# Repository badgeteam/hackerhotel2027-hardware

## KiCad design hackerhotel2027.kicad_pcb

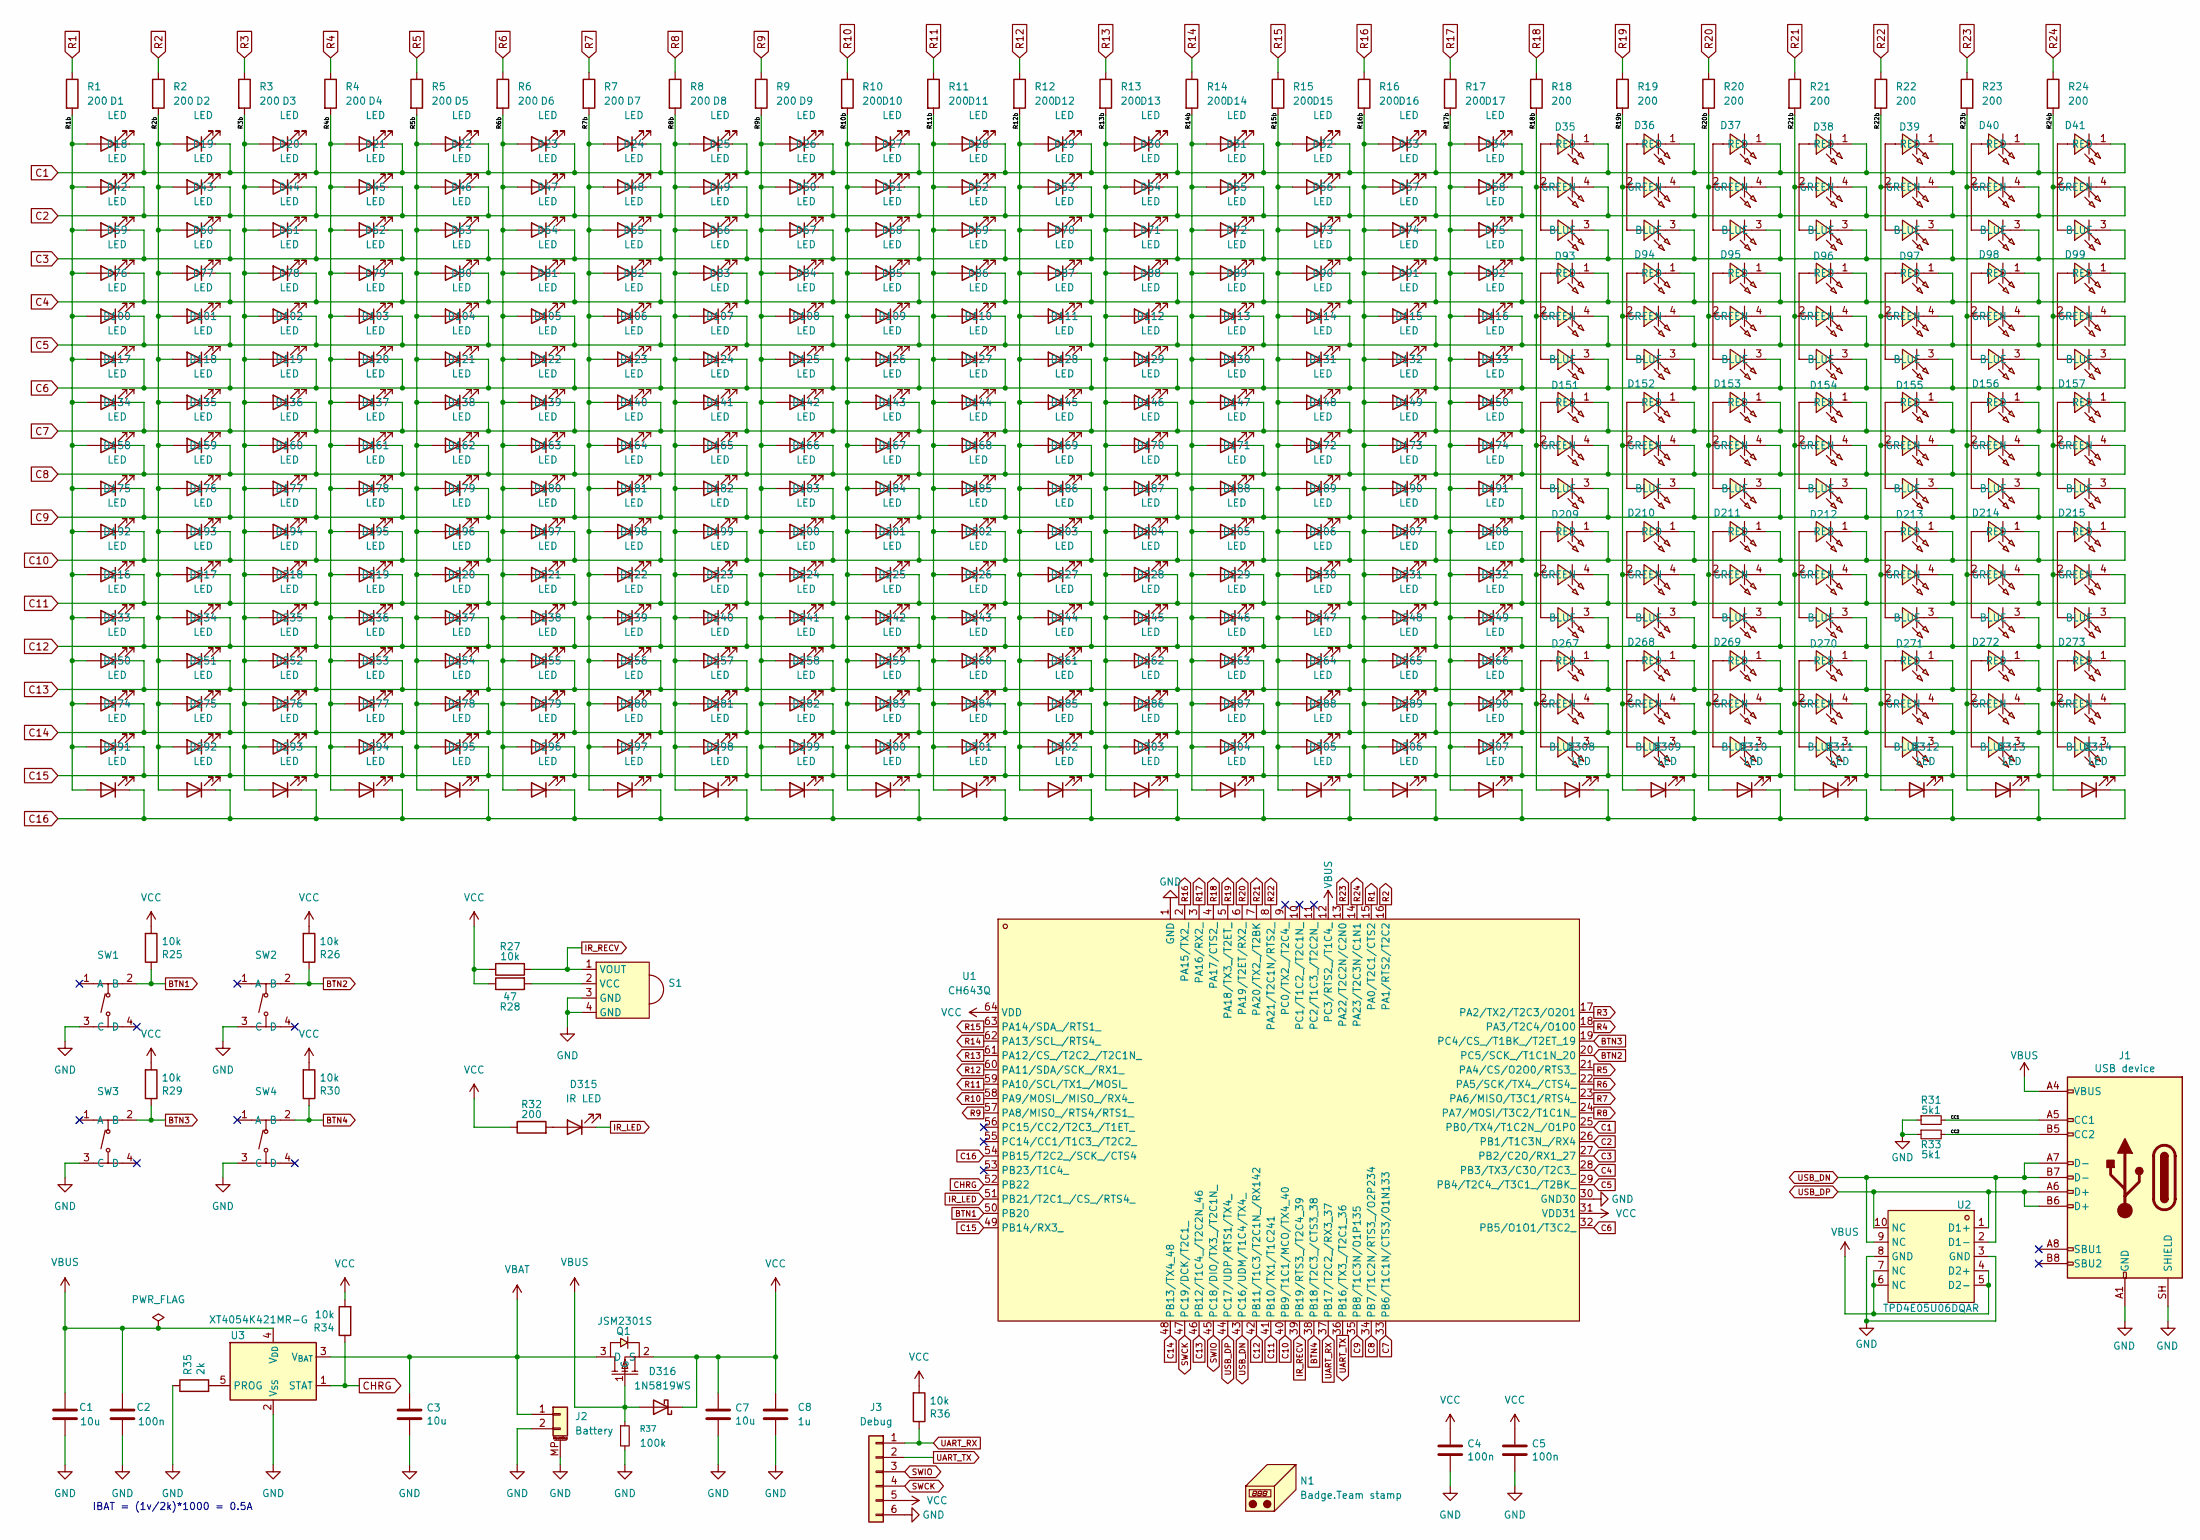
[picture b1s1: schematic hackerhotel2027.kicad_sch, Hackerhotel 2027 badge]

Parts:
C1, C3, C7: 10u; C_0603_1608Metric; LCSC Part C19702
C2: 100n; C_0402_1005Metric; LCSC Part C1525
C4, C5: 100n; C_0402_1005Metric; LCSC Part C307331
C8: 1u; C_0603_1608Metric; LCSC Part C5199872
D1, D2, D3, D4, D5, D6, D7, D8, D9, D10, D11, D12, D13, D14, D15, D16, D17, D18, D19, D20, D21, D22, D23, D24, D25, D26, D27, D28, D29, D30, D31, D32, D33, D34, D42, D43, D44, D45, D46, D47, D48, D49, D50, D51, D52, D53, D54, D55, D56, D57, D58, D59, D60, D61, D62, D63, D64, D65, D66, D67, D68, D69, D70, D71, D72, D73, D74, D75, D76, D77, D78, D79, D80, D81, D82, D83, D84, D85, D86, D87, D88, D89, D90, D91, D92, D100, D101, D102, D103, D104, D105, D106, D107, D108, D109, D110, D111, D112, D113, D114, D115, D116, D117, D118, D119, D120, D121, D122, D123, D124, D125, D126, D127, D128, D129, D130, D131, D132, D133, D134, D135, D136, D137, D138, D139, D140, D141, D142, D143, D144, D145, D146, D147, D148, D149, D150, D158, D159, D160, D161, D162, D163, D164, D165, D166, D167, D168, D169, D170, D171, D172, D173, D174, D175, D176, D177, D178, D179, D180, D181, D182, D183, D184, D185, D186, D187, D188, D189, D190, D191, D192, D193, D194, D195, D196, D197, D198, D199, D200, D201, D202, D203, D204, D205, D206, D207, D208, D216, D217, D218, D219, D220, D221, D222, D223, D224, D225, D226, D227, D228, D229, D230, D231, D232, D233, D234, D235, D236, D237, D238, D239, D240, D241, D242, D243, D244, D245, D246, D247, D248, D249, D250, D251, D252, D253, D254, D255, D256, D257, D258, D259, D260, D261, D262, D263, D264, D265, D266, D274, D275, D276, D277, D278, D279, D280, D281, D282, D283, D284, D285, D286, D287, D288, D289, D290, D291, D292, D293, D294, D295, D296, D297, D298, D299, D300, D301, D302, D303, D304, D305, D306, D307, D308, D309, D310, D311, D312, D313, D314: LED; LED_0402_1005Metric_nosilk; LCSC Part C52675968
D35, D36, D37, D38, D39, D40, D41, D93, D94, D95, D96, D97, D98, D99, D151, D152, D153, D154, D155, D156, D157, D209, D210, D211, D212, D213, D214, D215, D267, D268, D269, D270, D271, D272, D273: NH-B1515RGBA-GF; LED-SMD-4P-L1.6-W1.5_NH-B1515RGBA-GF; MPN NH-B1515RGBA-GF; LCSC Part C52212029
D315: IR LED; LED_0603_1608Metric; LCSC Part C965886
D316: 1N5819WS; D_SOD-323; LCSC Part C191023
J1: USB device; USB_C_Receptacle_HRO_TYPE-C-31-M-12; LCSC Part C165948
J2: Battery; CONN-SMD_PH-2AWB; LCSC Part C20598817
J3: Debug; PinHeader_1x06_P1.27mm_Vertical
N1: Badge.Team stamp; stamp_small
Q1: JSM2301S; SOT-23; LCSC Part C916399
R1, R2, R3, R4, R5, R6, R7, R8, R9, R10, R11, R12, R13, R14, R15, R16, R17, R18, R19, R20, R21, R22, R23, R24, R32: 200; R_0402_1005Metric; LCSC Part C25087
R25, R26, R27, R29, R30, R34, R36: 10k; R_0402_1005Metric; LCSC Part C25744
R28: 47; R_0402_1005Metric; LCSC Part C22369545
R31, R33: 5k1; R_0402_1005Metric; LCSC Part C25905
R35: 2k; R_0402_1005Metric; LCSC Part C4109
R37: 100k; R_0402_1005Metric; LCSC Part C25741
S1: DY-IRMHF384-T05-2.5KB; OPTO-SMD_4P-L3.9-W3.4_IRM-H432M3-R8; MPN DY-IRMHF384-T05-2.5KB; LCSC Part C7280961
SW1, SW2, SW3, SW4: TS-1187A-B-A-B; SW-SMD_4P-L5.1-W5.1-P3.70-LS6.5-TL_H1.5; MPN TS-1187A-B-A-B; LCSC Part C318884
U1: CH643Q; LQFP-64_L7.0-W7.0-P0.40-LS9.2-BL; MPN CH643Q; LCSC Part C22448687
U2: TPD4E05U06DQAR; USON-10_L2.5-W1.0-P0.50-BL; LCSC Part C138714
U3: XT4054K421MR-G; SOT-23-5; LCSC Part C141405

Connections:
/CC1: J1.A5 (CC1), R31.2
/CC2: J1.B5 (CC2), R33.2
/R1b: D1.2 (A), D18.2 (A), D42.2 (A), D59.2 (A), D76.2 (A), D100.2 (A), D117.2 (A), D134.2 (A), D158.2 (A), D175.2 (A), D192.2 (A), D216.2 (A), D233.2 (A), D250.2 (A), D274.2 (A), D291.2 (A), R1.2
/R2b: D2.2 (A), D19.2 (A), D43.2 (A), D60.2 (A), D77.2 (A), D101.2 (A), D118.2 (A), D135.2 (A), D159.2 (A), D176.2 (A), D193.2 (A), D217.2 (A), D234.2 (A), D251.2 (A), D275.2 (A), D292.2 (A), R2.2
/R3b: D3.2 (A), D20.2 (A), D44.2 (A), D61.2 (A), D78.2 (A), D102.2 (A), D119.2 (A), D136.2 (A), D160.2 (A), D177.2 (A), D194.2 (A), D218.2 (A), D235.2 (A), D252.2 (A), D276.2 (A), D293.2 (A), R3.2
/R4b: D4.2 (A), D21.2 (A), D45.2 (A), D62.2 (A), D79.2 (A), D103.2 (A), D120.2 (A), D137.2 (A), D161.2 (A), D178.2 (A), D195.2 (A), D219.2 (A), D236.2 (A), D253.2 (A), D277.2 (A), D294.2 (A), R4.2
/R5b: D5.2 (A), D22.2 (A), D46.2 (A), D63.2 (A), D80.2 (A), D104.2 (A), D121.2 (A), D138.2 (A), D162.2 (A), D179.2 (A), D196.2 (A), D220.2 (A), D237.2 (A), D254.2 (A), D278.2 (A), D295.2 (A), R5.2
/R6b: D6.2 (A), D23.2 (A), D47.2 (A), D64.2 (A), D81.2 (A), D105.2 (A), D122.2 (A), D139.2 (A), D163.2 (A), D180.2 (A), D197.2 (A), D221.2 (A), D238.2 (A), D255.2 (A), D279.2 (A), D296.2 (A), R6.2
/R7b: D7.2 (A), D24.2 (A), D48.2 (A), D65.2 (A), D82.2 (A), D106.2 (A), D123.2 (A), D140.2 (A), D164.2 (A), D181.2 (A), D198.2 (A), D222.2 (A), D239.2 (A), D256.2 (A), D280.2 (A), D297.2 (A), R7.2
/R8b: D8.2 (A), D25.2 (A), D49.2 (A), D66.2 (A), D83.2 (A), D107.2 (A), D124.2 (A), D141.2 (A), D165.2 (A), D182.2 (A), D199.2 (A), D223.2 (A), D240.2 (A), D257.2 (A), D281.2 (A), D298.2 (A), R8.2
/R9b: D9.2 (A), D26.2 (A), D50.2 (A), D67.2 (A), D84.2 (A), D108.2 (A), D125.2 (A), D142.2 (A), D166.2 (A), D183.2 (A), D200.2 (A), D224.2 (A), D241.2 (A), D258.2 (A), D282.2 (A), D299.2 (A), R9.2
/R10b: D10.2 (A), D27.2 (A), D51.2 (A), D68.2 (A), D85.2 (A), D109.2 (A), D126.2 (A), D143.2 (A), D167.2 (A), D184.2 (A), D201.2 (A), D225.2 (A), D242.2 (A), D259.2 (A), D283.2 (A), D300.2 (A), R10.2
/R11b: D11.2 (A), D28.2 (A), D52.2 (A), D69.2 (A), D86.2 (A), D110.2 (A), D127.2 (A), D144.2 (A), D168.2 (A), D185.2 (A), D202.2 (A), D226.2 (A), D243.2 (A), D260.2 (A), D284.2 (A), D301.2 (A), R11.2
/R12b: D12.2 (A), D29.2 (A), D53.2 (A), D70.2 (A), D87.2 (A), D111.2 (A), D128.2 (A), D145.2 (A), D169.2 (A), D186.2 (A), D203.2 (A), D227.2 (A), D244.2 (A), D261.2 (A), D285.2 (A), D302.2 (A), R12.2
/R13b: D13.2 (A), D30.2 (A), D54.2 (A), D71.2 (A), D88.2 (A), D112.2 (A), D129.2 (A), D146.2 (A), D170.2 (A), D187.2 (A), D204.2 (A), D228.2 (A), D245.2 (A), D262.2 (A), D286.2 (A), D303.2 (A), R13.2
/R14b: D14.2 (A), D31.2 (A), D55.2 (A), D72.2 (A), D89.2 (A), D113.2 (A), D130.2 (A), D147.2 (A), D171.2 (A), D188.2 (A), D205.2 (A), D229.2 (A), D246.2 (A), D263.2 (A), D287.2 (A), D304.2 (A), R14.2
/R15b: D15.2 (A), D32.2 (A), D56.2 (A), D73.2 (A), D90.2 (A), D114.2 (A), D131.2 (A), D148.2 (A), D172.2 (A), D189.2 (A), D206.2 (A), D230.2 (A), D247.2 (A), D264.2 (A), D288.2 (A), D305.2 (A), R15.2
/R16b: D16.2 (A), D33.2 (A), D57.2 (A), D74.2 (A), D91.2 (A), D115.2 (A), D132.2 (A), D149.2 (A), D173.2 (A), D190.2 (A), D207.2 (A), D231.2 (A), D248.2 (A), D265.2 (A), D289.2 (A), D306.2 (A), R16.2
/R17b: D17.2 (A), D34.2 (A), D58.2 (A), D75.2 (A), D92.2 (A), D116.2 (A), D133.2 (A), D150.2 (A), D174.2 (A), D191.2 (A), D208.2 (A), D232.2 (A), D249.2 (A), D266.2 (A), D290.2 (A), D307.2 (A), R17.2
/R18b: D35.2, D93.2, D151.2, D209.2, D267.2, D308.2 (A), R18.2
/R19b: D36.2, D94.2, D152.2, D210.2, D268.2, D309.2 (A), R19.2
/R20b: D37.2, D95.2, D153.2, D211.2, D269.2, D310.2 (A), R20.2
/R21b: D38.2, D96.2, D154.2, D212.2, D270.2, D311.2 (A), R21.2
/R22b: D39.2, D97.2, D155.2, D213.2, D271.2, D312.2 (A), R22.2
/R23b: D40.2, D98.2, D156.2, D214.2, D272.2, D313.2 (A), R23.2
/R24b: D41.2, D99.2, D157.2, D215.2, D273.2, D314.2 (A), R24.2
BTN1: R25.1, SW1.2 (B), U1.50 (PB20)
BTN2: R26.1, SW2.2 (B), U1.20 (PC5/SCK_/T1C1N_20)
BTN3: R29.1, SW3.2 (B), U1.19 (PC4/CS_/T1BK_/T2ET_19)
BTN4: R30.1, SW4.2 (B), U1.38 (PB18/T2C3_/CTS3_38)
C1: D1.1 (K), D2.1 (K), D3.1 (K), D4.1 (K), D5.1 (K), D6.1 (K), D7.1 (K), D8.1 (K), D9.1 (K), D10.1 (K), D11.1 (K), D12.1 (K), D13.1 (K), D14.1 (K), D15.1 (K), D16.1 (K), D17.1 (K), D35.1 (RED), D36.1 (RED), D37.1 (RED), D38.1 (RED), D39.1 (RED), D40.1 (RED), D41.1 (RED), U1.25 (PB0/TX4/T1C2N_/O1P0)
C2: D18.1 (K), D19.1 (K), D20.1 (K), D21.1 (K), D22.1 (K), D23.1 (K), D24.1 (K), D25.1 (K), D26.1 (K), D27.1 (K), D28.1 (K), D29.1 (K), D30.1 (K), D31.1 (K), D32.1 (K), D33.1 (K), D34.1 (K), D35.4 (GREEN), D36.4 (GREEN), D37.4 (GREEN), D38.4 (GREEN), D39.4 (GREEN), D40.4 (GREEN), D41.4 (GREEN), U1.26 (PB1/T1C3N_/RX4)
C3: D35.3 (BLUE), D36.3 (BLUE), D37.3 (BLUE), D38.3 (BLUE), D39.3 (BLUE), D40.3 (BLUE), D41.3 (BLUE), D42.1 (K), D43.1 (K), D44.1 (K), D45.1 (K), D46.1 (K), D47.1 (K), D48.1 (K), D49.1 (K), D50.1 (K), D51.1 (K), D52.1 (K), D53.1 (K), D54.1 (K), D55.1 (K), D56.1 (K), D57.1 (K), D58.1 (K), U1.27 (PB2/C2O/RX1_27)
C4: D59.1 (K), D60.1 (K), D61.1 (K), D62.1 (K), D63.1 (K), D64.1 (K), D65.1 (K), D66.1 (K), D67.1 (K), D68.1 (K), D69.1 (K), D70.1 (K), D71.1 (K), D72.1 (K), D73.1 (K), D74.1 (K), D75.1 (K), D93.1 (RED), D94.1 (RED), D95.1 (RED), D96.1 (RED), D97.1 (RED), D98.1 (RED), D99.1 (RED), U1.28 (PB3/TX3/C3O/T2C3_)
C5: D76.1 (K), D77.1 (K), D78.1 (K), D79.1 (K), D80.1 (K), D81.1 (K), D82.1 (K), D83.1 (K), D84.1 (K), D85.1 (K), D86.1 (K), D87.1 (K), D88.1 (K), D89.1 (K), D90.1 (K), D91.1 (K), D92.1 (K), D93.4 (GREEN), D94.4 (GREEN), D95.4 (GREEN), D96.4 (GREEN), D97.4 (GREEN), D98.4 (GREEN), D99.4 (GREEN), U1.29 (PB4/T2C4_/T3C1_/T2BK_)
C6: D93.3 (BLUE), D94.3 (BLUE), D95.3 (BLUE), D96.3 (BLUE), D97.3 (BLUE), D98.3 (BLUE), D99.3 (BLUE), D100.1 (K), D101.1 (K), D102.1 (K), D103.1 (K), D104.1 (K), D105.1 (K), D106.1 (K), D107.1 (K), D108.1 (K), D109.1 (K), D110.1 (K), D111.1 (K), D112.1 (K), D113.1 (K), D114.1 (K), D115.1 (K), D116.1 (K), U1.32 (PB5/O1O1/T3C2_)
C7: D117.1 (K), D118.1 (K), D119.1 (K), D120.1 (K), D121.1 (K), D122.1 (K), D123.1 (K), D124.1 (K), D125.1 (K), D126.1 (K), D127.1 (K), D128.1 (K), D129.1 (K), D130.1 (K), D131.1 (K), D132.1 (K), D133.1 (K), D151.1 (RED), D152.1 (RED), D153.1 (RED), D154.1 (RED), D155.1 (RED), D156.1 (RED), D157.1 (RED), U1.33 (PB6/T1C1N/CTS3/O1N133)
C8: D134.1 (K), D135.1 (K), D136.1 (K), D137.1 (K), D138.1 (K), D139.1 (K), D140.1 (K), D141.1 (K), D142.1 (K), D143.1 (K), D144.1 (K), D145.1 (K), D146.1 (K), D147.1 (K), D148.1 (K), D149.1 (K), D150.1 (K), D151.4 (GREEN), D152.4 (GREEN), D153.4 (GREEN), D154.4 (GREEN), D155.4 (GREEN), D156.4 (GREEN), D157.4 (GREEN), U1.34 (PB7/T1C2N/RTS3_/O2P234)
C9: D151.3 (BLUE), D152.3 (BLUE), D153.3 (BLUE), D154.3 (BLUE), D155.3 (BLUE), D156.3 (BLUE), D157.3 (BLUE), D158.1 (K), D159.1 (K), D160.1 (K), D161.1 (K), D162.1 (K), D163.1 (K), D164.1 (K), D165.1 (K), D166.1 (K), D167.1 (K), D168.1 (K), D169.1 (K), D170.1 (K), D171.1 (K), D172.1 (K), D173.1 (K), D174.1 (K), U1.35 (PB8/T1C3N/O1P135)
C10: D175.1 (K), D176.1 (K), D177.1 (K), D178.1 (K), D179.1 (K), D180.1 (K), D181.1 (K), D182.1 (K), D183.1 (K), D184.1 (K), D185.1 (K), D186.1 (K), D187.1 (K), D188.1 (K), D189.1 (K), D190.1 (K), D191.1 (K), D209.1 (RED), D210.1 (RED), D211.1 (RED), D212.1 (RED), D213.1 (RED), D214.1 (RED), D215.1 (RED), U1.40 (PB9/T1C1/MCO/TX4_40)
C11: D192.1 (K), D193.1 (K), D194.1 (K), D195.1 (K), D196.1 (K), D197.1 (K), D198.1 (K), D199.1 (K), D200.1 (K), D201.1 (K), D202.1 (K), D203.1 (K), D204.1 (K), D205.1 (K), D206.1 (K), D207.1 (K), D208.1 (K), D209.4 (GREEN), D210.4 (GREEN), D211.4 (GREEN), D212.4 (GREEN), D213.4 (GREEN), D214.4 (GREEN), D215.4 (GREEN), U1.41 (PB10/TX1/T1C241)
C12: D209.3 (BLUE), D210.3 (BLUE), D211.3 (BLUE), D212.3 (BLUE), D213.3 (BLUE), D214.3 (BLUE), D215.3 (BLUE), D216.1 (K), D217.1 (K), D218.1 (K), D219.1 (K), D220.1 (K), D221.1 (K), D222.1 (K), D223.1 (K), D224.1 (K), D225.1 (K), D226.1 (K), D227.1 (K), D228.1 (K), D229.1 (K), D230.1 (K), D231.1 (K), D232.1 (K), U1.42 (PB11/T1C3/T2C1N_/RX142)
C13: D233.1 (K), D234.1 (K), D235.1 (K), D236.1 (K), D237.1 (K), D238.1 (K), D239.1 (K), D240.1 (K), D241.1 (K), D242.1 (K), D243.1 (K), D244.1 (K), D245.1 (K), D246.1 (K), D247.1 (K), D248.1 (K), D249.1 (K), D267.1 (RED), D268.1 (RED), D269.1 (RED), D270.1 (RED), D271.1 (RED), D272.1 (RED), D273.1 (RED), U1.46 (PB12/T1C4_/T2C2N_46)
C14: D250.1 (K), D251.1 (K), D252.1 (K), D253.1 (K), D254.1 (K), D255.1 (K), D256.1 (K), D257.1 (K), D258.1 (K), D259.1 (K), D260.1 (K), D261.1 (K), D262.1 (K), D263.1 (K), D264.1 (K), D265.1 (K), D266.1 (K), D267.4 (GREEN), D268.4 (GREEN), D269.4 (GREEN), D270.4 (GREEN), D271.4 (GREEN), D272.4 (GREEN), D273.4 (GREEN), U1.48 (PB13/TX4_48)
C15: D267.3 (BLUE), D268.3 (BLUE), D269.3 (BLUE), D270.3 (BLUE), D271.3 (BLUE), D272.3 (BLUE), D273.3 (BLUE), D274.1 (K), D275.1 (K), D276.1 (K), D277.1 (K), D278.1 (K), D279.1 (K), D280.1 (K), D281.1 (K), D282.1 (K), D283.1 (K), D284.1 (K), D285.1 (K), D286.1 (K), D287.1 (K), D288.1 (K), D289.1 (K), D290.1 (K), U1.49 (PB14/RX3_)
C16: D291.1 (K), D292.1 (K), D293.1 (K), D294.1 (K), D295.1 (K), D296.1 (K), D297.1 (K), D298.1 (K), D299.1 (K), D300.1 (K), D301.1 (K), D302.1 (K), D303.1 (K), D304.1 (K), D305.1 (K), D306.1 (K), D307.1 (K), D308.1 (K), D309.1 (K), D310.1 (K), D311.1 (K), D312.1 (K), D313.1 (K), D314.1 (K), U1.54 (PB15/T2C2_/SCK_/CTS4)
CHRG: R34.1, U1.52 (PB22), U3.1 (STAT)
GND: C1.1, C2.1, C3.2, C4.2, C5.2, C7.2, C8.2, J1.A1 (GND), J1.A12 (GND), J1.B1 (GND), J1.B12 (GND), J1.SH (SHIELD), J2.2, J2.MP (MountPin), J3.6, R31.1, R33.1, R35.1, R37.2, S1.3 (GND), S1.4 (GND), SW1.3 (C), SW2.3 (C), SW3.3 (C), SW4.3 (C), U1.1 (GND), U1.30 (GND30), U2.3 (GND), U2.8 (GND), U3.2 (V_{SS})
IR_LED: D315.1 (K), U1.51 (PB21/T2C1_/CS_/RTS4_)
IR_RECV: R27.2, S1.1 (VOUT), U1.39 (PB19/RTS3_/T2C4_39)
unnamed: D315.2 (A), R32.2
unnamed: R28.2, S1.2 (VCC)
unnamed: R35.2, U3.5 (PROG)
R1: R1.1, U1.15 (PA0/T2C1/CTS2)
R2: R2.1, U1.16 (PA1/RTS2/T2C2)
R3: R3.1, U1.17 (PA2/TX2/T2C3/O2O1)
R4: R4.1, U1.18 (PA3/T2C4/O1O0)
R5: R5.1, U1.21 (PA4/CS/O2O0/RTS3_)
R6: R6.1, U1.22 (PA5/SCK/TX4_/CTS4_)
R7: R7.1, U1.23 (PA6/MISO/T3C1/RTS4_)
R8: R8.1, U1.24 (PA7/MOSI/T3C2/T1C1N_)
R9: R9.1, U1.57 (PA8/MISO_/RTS4/RTS1_)
R10: R10.1, U1.58 (PA9/MOSI_/MISO_/RX4_)
R11: R11.1, U1.59 (PA10/SCL/TX1_/MOSI_)
R12: R12.1, U1.60 (PA11/SDA/SCK_/RX1_)
R13: R13.1, U1.61 (PA12/CS_/T2C2_/T2C1N_)
R14: R14.1, U1.62 (PA13/SCL_/RTS4_)
R15: R15.1, U1.63 (PA14/SDA_/RTS1_)
R16: R16.1, U1.2 (PA15/TX2_)
R17: R17.1, U1.3 (PA16/RX2_)
R18: R18.1, U1.4 (PA17/CTS2_)
R19: R19.1, U1.5 (PA18/TX3_/T2ET_)
R20: R20.1, U1.6 (PA19/T2ET/RX2_)
R21: R21.1, U1.7 (PA20/TX2_/T2BK)
R22: R22.1, U1.8 (PA21/T2C1N/RTS2_)
R23: R23.1, U1.13 (PA22/T2C2N/C2N0)
R24: R24.1, U1.14 (PA23/T2C3N/C1N1)
SWCK: J3.4, U1.47 (PC19/DCK/T2C1_)
SWIO: J3.3, U1.45 (PC18/DIO/TX3_/T2C1N_)
UART_RX: J3.1, R36.1, U1.37 (PB17/T2C2_/RX3_37)
UART_TX: J3.2, U1.36 (PB16/TX3_/T2C1_36)
USB_DN: J1.A7 (D-), J1.B7 (D-), U1.43 (PC16/UDM/T1C4/TX4_), U2.2 (D1-), U2.9 (NC)
USB_DP: J1.A6 (D+), J1.B6 (D+), U1.44 (PC17/UDP/RTS1/TX4_), U2.1 (D1+), U2.10 (NC)
VBAT: C3.1, J2.1, Q1.3 (D), U3.3 (V_{BAT})
VBUS: C1.2, C2.2, D316.2 (A), J1.A4 (VBUS), J1.A9 (VBUS), J1.B4 (VBUS), J1.B9 (VBUS), Q1.1 (G), R37.1, U1.12 (PC3/RTS2_/T1C4_), U2.4 (D2+), U2.5 (D2-), U2.6 (NC), U2.7 (NC), U3.4 (V_{DD})
VCC: C4.1, C5.1, C7.1, C8.1, D316.1 (K), J3.5, Q1.2 (S), R25.2, R26.2, R27.1, R28.1, R29.2, R30.2, R32.1, R34.2, R36.2, U1.31 (VDD31), U1.64 (VDD)

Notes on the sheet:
IBAT = (1v/2k)*1000 = 0.5A

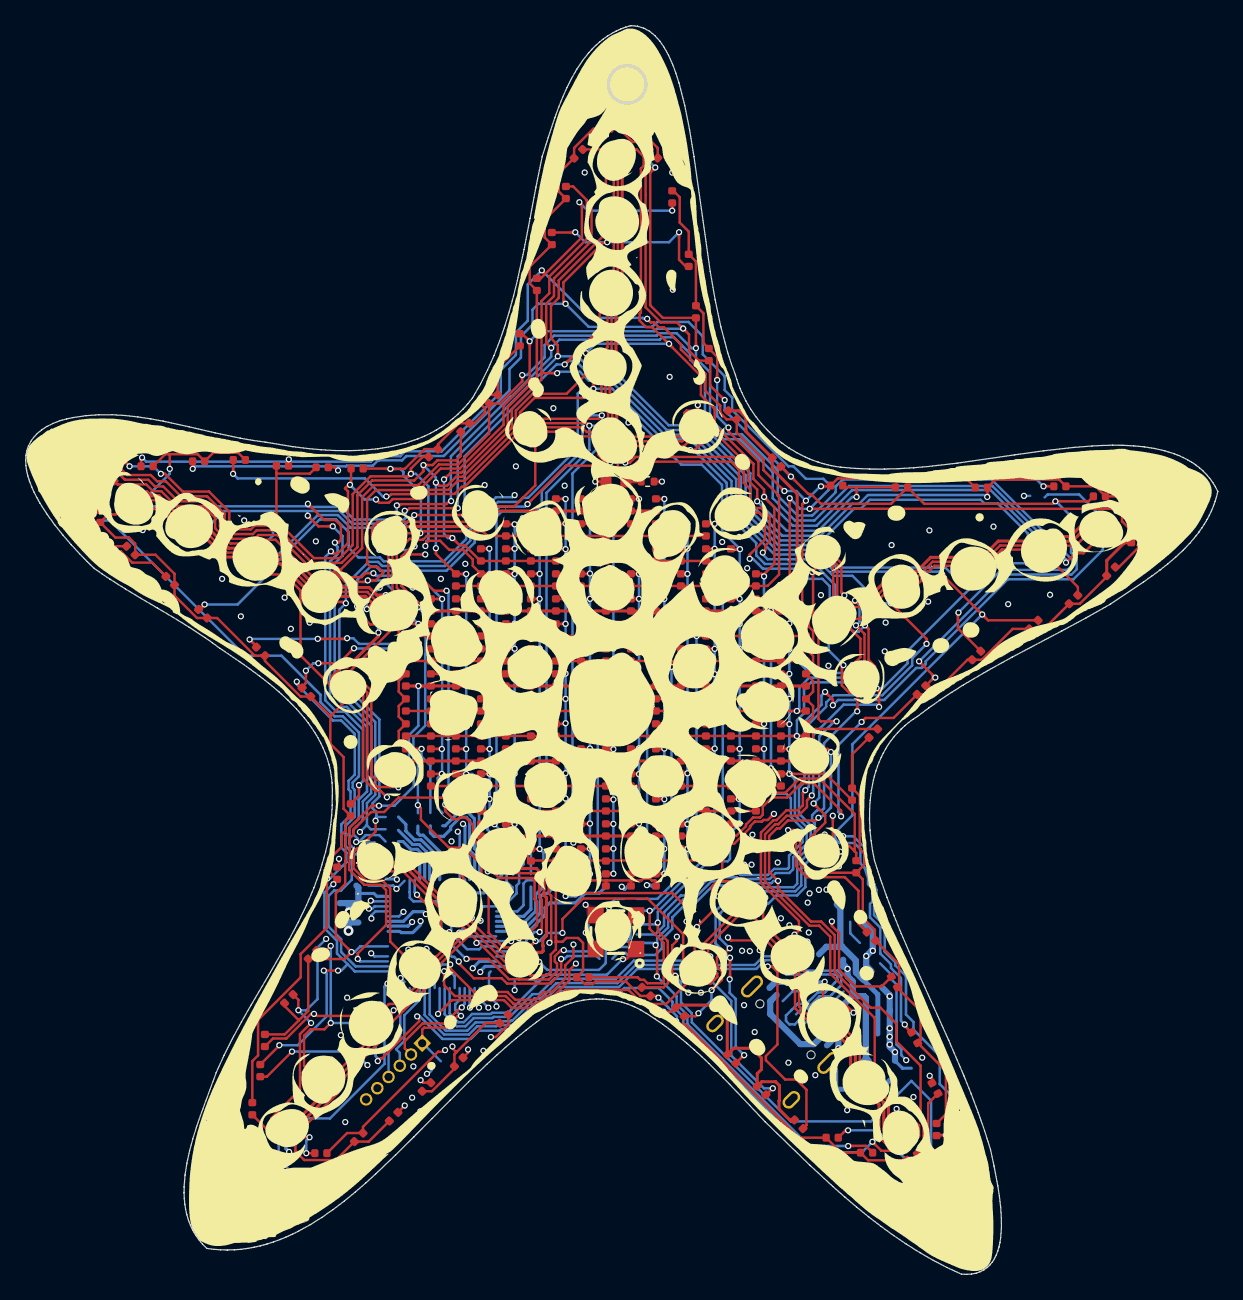
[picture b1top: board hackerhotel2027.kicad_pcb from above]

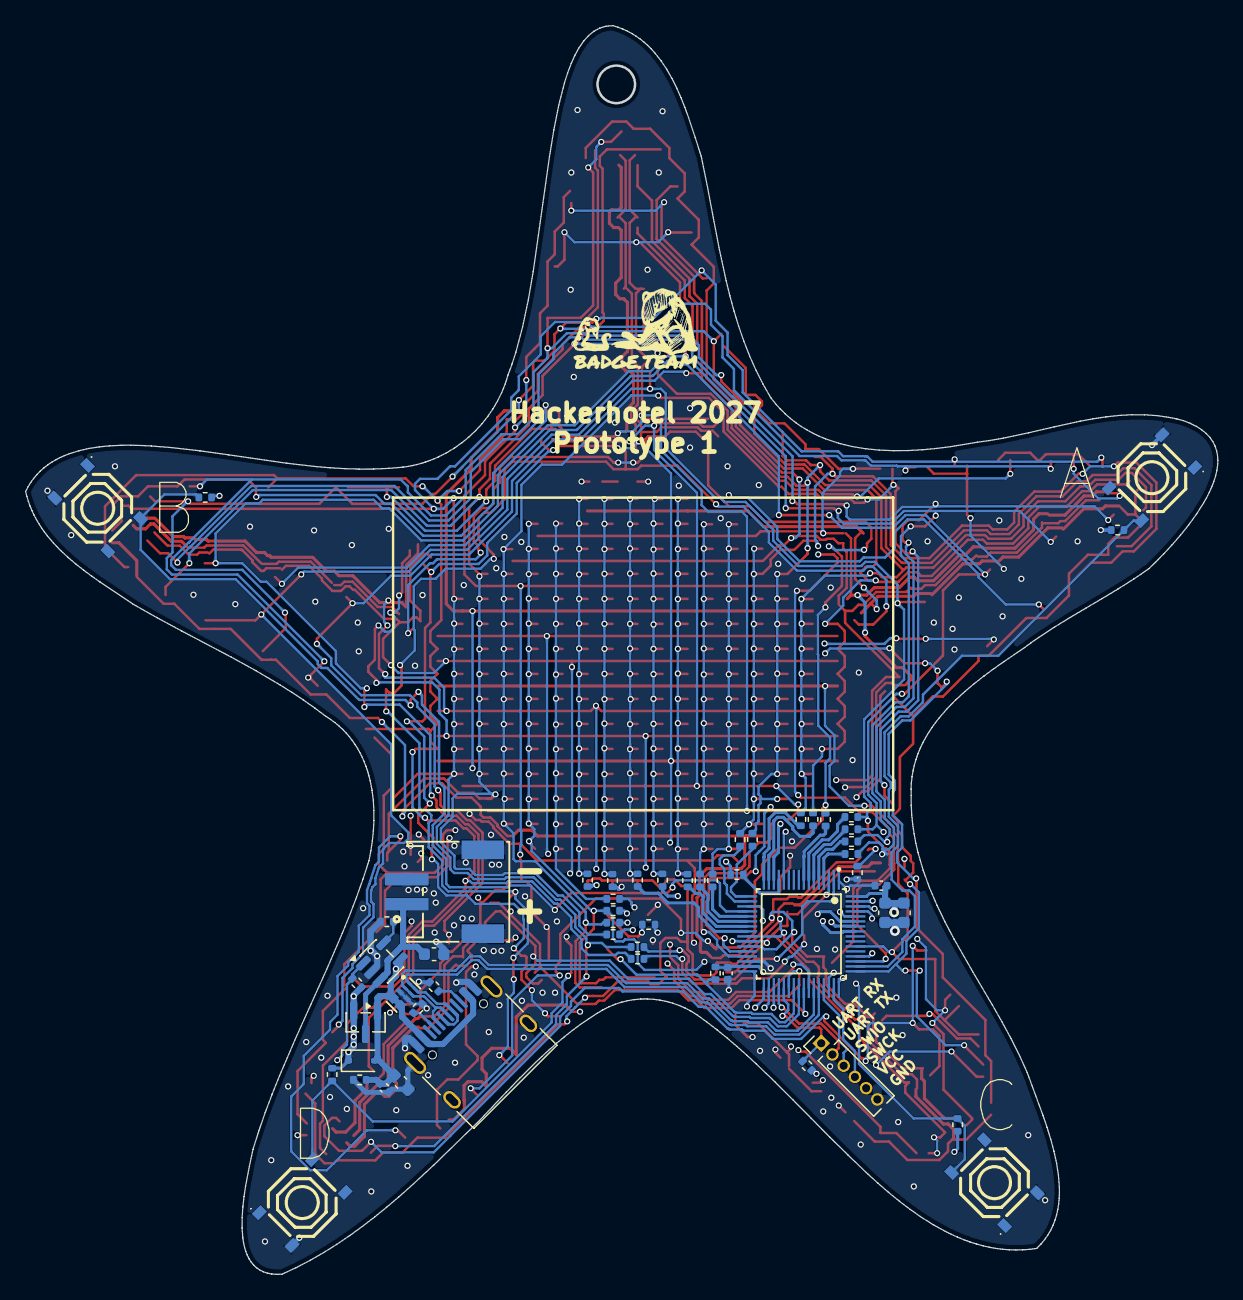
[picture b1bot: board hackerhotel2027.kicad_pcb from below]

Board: 6 copper layers, 95.4 x 99.9 mm, 373 parts (56 on the bottom side), 86 nets.

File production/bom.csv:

Designator,Footprint,Quantity,Value,LCSC Part #
"C1, C3, C7",0603,3,10u,C19702
C2,0402,1,100n,C1525
"C4, C5",0402,2,100n,C307331
C8,0603,1,1u,C5199872
"D1, D10, D100, D101, D102, D103, D104, D105, D106, D107, D108, D109, D11, D110, D111, D112, D113, D114, D115, D116, D117, D118, D119, D12, D120, D121, D122, D123, D124, D125, D126, D127, D128, D129, D13, D130, D131, D132, D133, D134, D135, D136, D137, D138, D139, D14, D140, D141, D142, D143, D144, D145, D146, D147, D148, D149, D15, D150, D158, D159, D16, D160, D161, D162, D163, D164, D165, D166, D167, D168, D169, D17, D170, D171, D172, D173, D174, D175, D176, D177, D178, D179, D18, D180, D181, D182, D183, D184, D185, D186, D187, D188, D189, D19, D190, D191, D192, D193, D194, D195, D196, D197, D198, D199, D2, D20, D200, D201, D202, D203, D204, D205, D206, D207, D208, D21, D216, D217, D218, D219, D22, D220, D221, D222, D223, D224, D225, D226, D227, D228, D229, D23, D230, D231, D232, D233, D234, D235, D236, D237, D238, D239, D24, D240, D241, D242, D243, D244, D245, D246, D247, D248, D249, D25, D250, D251, D252, D253, D254, D255, D256, D257, D258, D259, D26, D260, D261, D262, D263, D264, D265, D266, D27, D274, D275, D276, D277, D278, D279, D28, D280, D281, D282, D283, D284, D285, D286, D287, D288, D289, D29, D290, D291, D292, D293, D294, D295, D296, D297, D298",0402,200,LED,C52675968
"D151, D152, D153, D154, D155, D156, D157, D209, D210, D211, D212, D213, D214, D215, D267, D268, D269, D270, D271, D272, D273, D35, D36, D37, D38, D39, D40, D41, D93, D94, D95, D96, D97, D98, D99",LED-SMD-4P-L1.6-W1.5_NH-B1515RGBA-GF,35,NH-B1515RGBA-GF,C52212029
"D299, D3, D30, D300, D301, D302, D303, D304, D305, D306, D307, D308, D309, D31, D310, D311, D312, D313, D314, D32, D33, D34, D4, D42, D43, D44, D45, D46, D47, D48, D49, D5, D50, D51, D52, D53, D54, D55, D56, D57, D58, D59, D6, D60, D61, D62, D63, D64, D65, D66, D67, D68, D69, D7, D70, D71, D72, D73, D74, D75, D76, D77, D78, D79, D8, D80, D81, D82, D83, D84, D85, D86, D87, D88, D89, D9, D90, D91, D92",0402,79,LED,C52675968
D315,0603,1,IR LED,C965886
D316,D_SOD-323,1,1N5819WS,C191023
J1,USB_C_Receptacle_HRO_TYPE-C-31-M-12,1,USB device,C165948
J2,CONN-SMD_PH-2AWB,1,Battery,C20598817
Q1,SOT-23,1,JSM2301S,C916399
"R1, R10, R11, R12, R13, R14, R15, R16, R17, R18, R19, R2, R20, R21, R22, R23, R24, R3, R32, R4, R5, R6, R7, R8, R9",0402,25,200,C25087
"R25, R26, R27, R29, R30, R34, R36",0402,7,10k,C25744
R28,0402,1,47,C22369545
"R31, R33",0402,2,5k1,C25905
R35,0402,1,2k,C4109
R37,0402,1,100k,C25741
S1,OPTO-SMD_4P-L3.9-W3.4_IRM-H432M3-R8,1,DY-IRMHF384-T05-2.5KB,C7280961
"SW1, SW2, SW3, SW4",SW-SMD_4P-L5.1-W5.1-P3.70-LS6.5-TL_H1.5,4,TS-1187A-B-A-B,C318884
U1,LQFP-64_L7.0-W7.0-P0.40-LS9.2-BL,1,CH643Q,C22448687
U2,USON-10_L2.5-W1.0-P0.50-BL,1,TPD4E05U06DQAR,C138714
U3,SOT-23-5,1,XT4054K421MR-G,C141405

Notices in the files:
hackerhotel2027.kicad_sch:
Copyright Stichting Badge.Team 2026
License: CERN-OHL-P
